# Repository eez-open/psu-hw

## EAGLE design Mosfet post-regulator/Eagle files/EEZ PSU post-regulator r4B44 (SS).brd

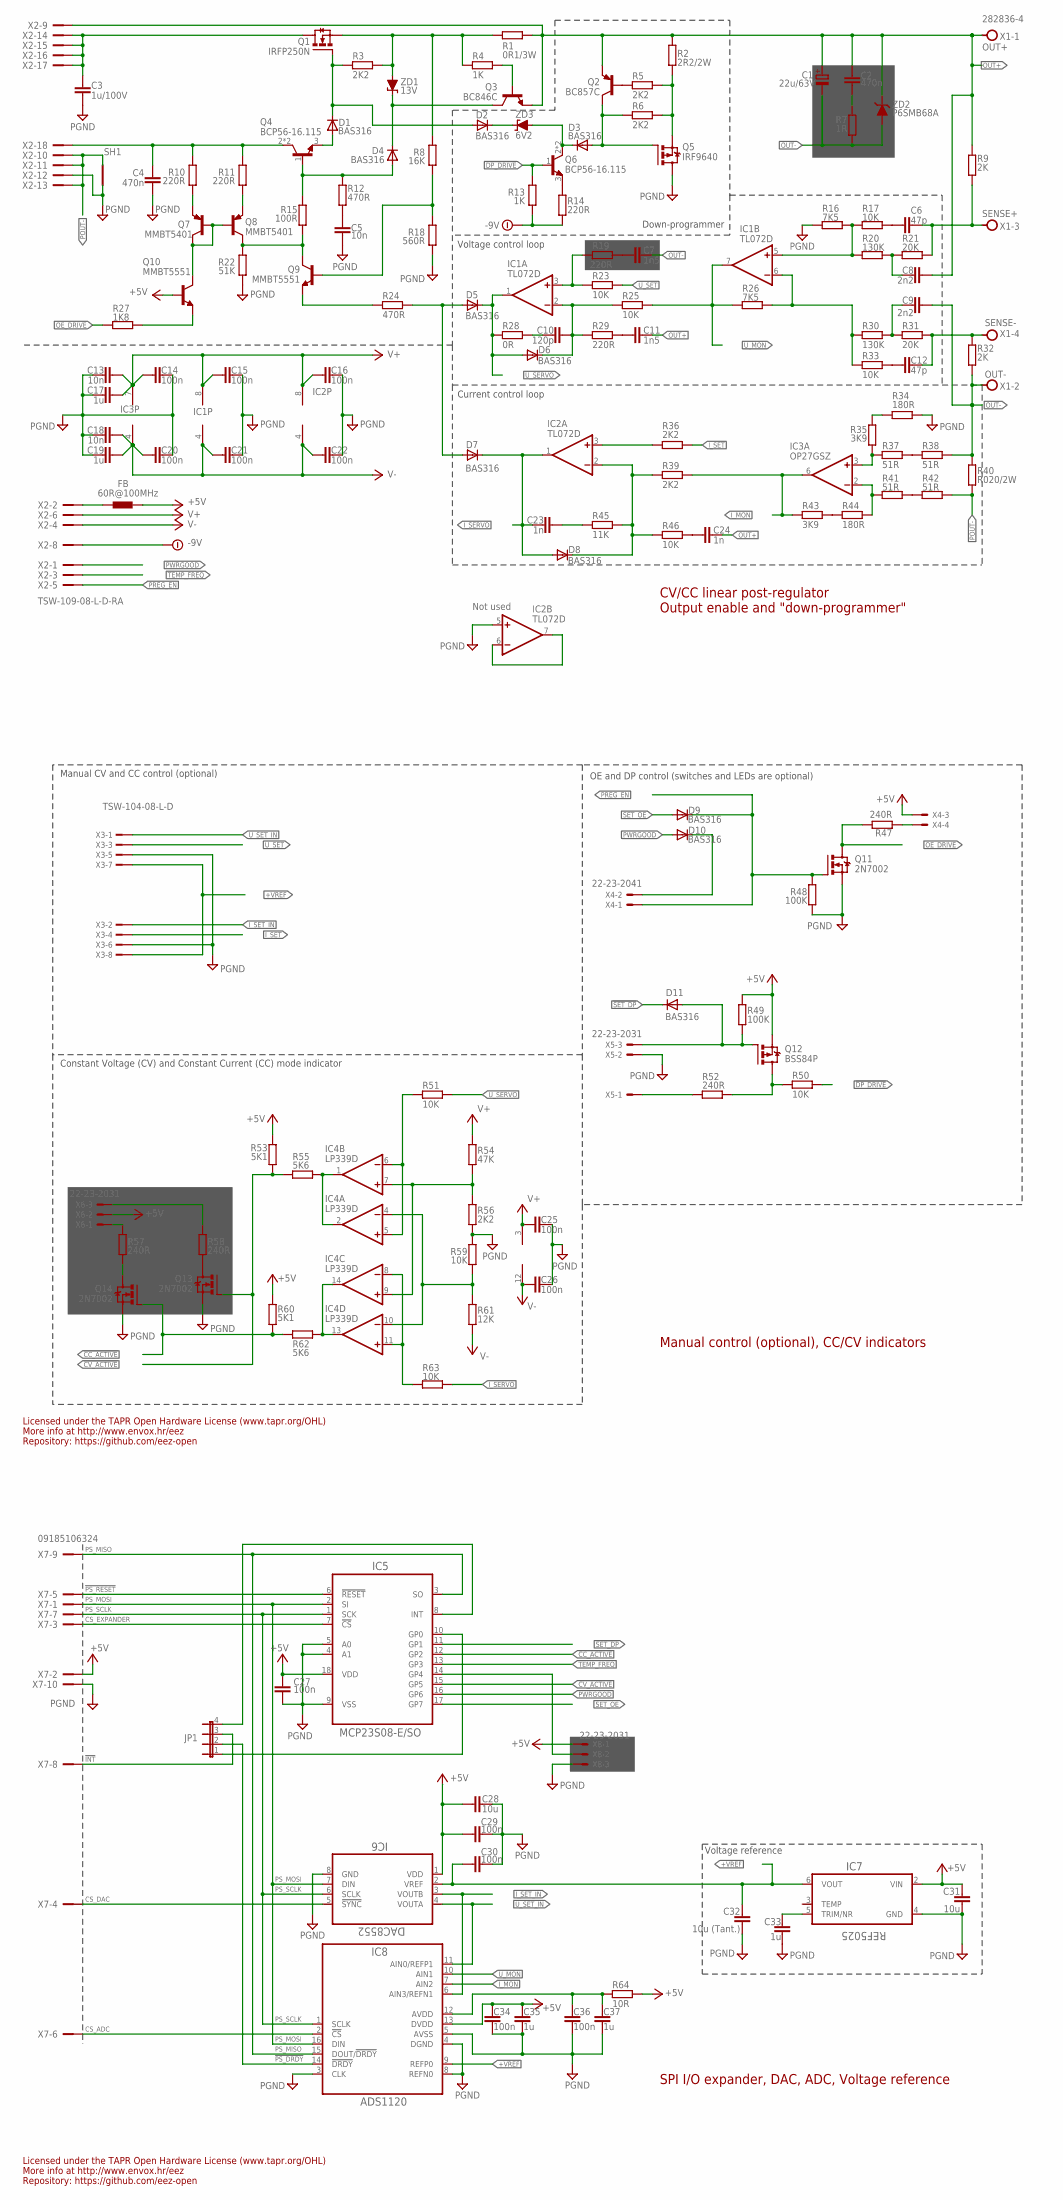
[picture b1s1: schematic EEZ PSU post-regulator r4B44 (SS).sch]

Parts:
C1: 22u/63V; CAPAE660X610N_COMBO2
C2, C4: 470n; C1812
C3: 1u/100V; C1206
C5, C13, C18: 10n; C0805
C6, C12: 47p; C0805
C7, C11: 1n5; C0805
C8, C9: 2n2; C0805
C10: 120p; C0805
C14, C15, C16, C20, C21, C22, C25, C26, C27, C29, C30, C34, C36: 100n; C0603
C17, C19, C33, C35, C37: 1u; C0805
C23, C24: 1n; C0805
C28, C31: 10u; C1206
C32: 10u (Tant.); C1206
D1, D2, D3, D4, D5, D6, D7, D8, D9, D10, D11: BAS316; SOD323-W
FB: 60R@100MHz; BEAD0603
IC1, IC2: TL072D; SOIC127P600X173-8N
IC3: OP27GSZ; SOIC127P600X173-8N
IC4: LP339D; SO14
IC5: MCP23S08-E/SO; SOIC127P1030X265-18N
IC6: DAC8552; DGK8-M
IC7: REF5025; SOIC127P600X175-8N
IC8: ADS1120; PW(R-PDSO-G16)
JP1: JP4E; JP4
Q1: IRFP250N; TO247BV
Q2: BC857C; SOT23-BEC
Q3: BC846C; SOT23-BEC
Q4, Q6: BCP56-16.115; SOT230P700X180-4N
Q5: IRF9640; TO220B-VMOS
Q7, Q8: MMBT5401; SOT23-BEC
Q9, Q10: MMBT5551; SOT23-BEC
Q11: 2N7002; SOT103P240X110-3N; MPN 2N7002-7-F
Q12: BSS84P; SOT95P237X112-3N
Q13, Q14: 2N7002; SOT103P240X110-3N
R1: 0R1/3W; 0411V
R2: 2R2/2W; 0411V
R3, R5, R6, R36, R39, R56: 2K2; R0805
R4, R13: 1K; R0805
R7: 1R; R0805
R8: 16K; R0805
R9, R32: 2K; R0805
R10, R11, R14, R19, R29: 220R; R0805
R12, R24: 470R; R0805
R15: 100R; R0805
R16, R26: 7K5; R0805
R17, R23, R25, R33, R46, R50, R51, R59, R63: 10K; R0805
R18: 560R; R0805
R20, R30: 130K; R0805
R21, R31: 20K; R0805
R22: 51K; R0805
R27: 1K8; R0805
R28: 0R; R0805
R34, R44: 180R; R0805
R35, R43: 3K9; R0805
R37, R38, R41, R42: 51R; R0805
R40: R020/2W; R2512
R45: 11K; R0805
R47, R52, R57, R58: 240R; R0805
R48, R49: 100K; R0805
R53, R60: 5K1; R0805
R54: 47K; R0805
R55, R62: 5K6; R0805
R61: 12K; R0805
R64: 10R; R0805
SH1: GND; SHORT
X1: 282836-4; TBLOCK5.0_4
X2: TSW-109-08-L-D-RA; FARNELL 2032801
X3: TSW-104-08-L-D; TSW-104-02-S-D
X4: 22-23-2041; MPN 22-23-2041
X5, X6, X8: 22-23-2031; MPN 22-23-2031
X7: 09185106324; PAK100/2500-10
ZD1: 13V; MINIMELF
ZD2: P6SMB68A; DO214AA
ZD3: 6V2; MINIMELF

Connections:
!CC_ACTIVE: IC5.12 (GP2), Q14.1 (G), R60.1, R62.2
!CV_ACTIVE: IC5.15 (GP5), Q13.1 (G), R53.1, R55.2
!DP_DRIVE: Q6.1 (B), R13.1, R50.1
!INT: JP1.3, X7.8
!PS_DRDY: IC8.14 (!DRDY), JP1.2
!PS_RESET: IC5.6 (!RESET), X7.5
!SET_DP: D11.C, IC5.11 (GP1)
+5V: C27.1, C28.1, C29.2, C31.1, C34.2, C35.2, FB.P$2 (2), IC5.18 (VDD), IC6.1 (VDD), IC7.2 (VIN), IC8.13 (DVDD), Q10.B, Q12.2 (S), R49.1, R53.2, R60.2, R64.1, X4.3, X6.2, X7.2, X8.1
+VREF: C30.2, C32.1, IC6.2 (VREF), IC7.6 (VOUT), IC8.9 (REFP0), X3.7, X3.8
-9V: R13.2, R14.2, X2.8
BATT_NTC: IC5.14 (GP4), X8.2
CC_LED: R57.2, X6.1
CS_ADC: IC8.2 (!CS), X7.6
CS_DAC: IC6.5 (!SYNC), X7.4
CS_EXPANDER: IC5.7 (!CS), X7.3
CV_LED: R58.1, X6.3
DC_IN: C3.1, Q1.D, X2.14, X2.15, X2.16, X2.17
DP_LED: Q12.3 (D), R50.2, R52.2
GND: C3.2, C4.2, C5.2, C13.1, C14.2, C15.1, C16.1, C17.1, C18.1, C19.1, C20.2, C21.1, C22.1, C25.1, C26.1, C27.2, C28.2, C29.1, C30.1, C31.2, C32.2, C33.2, C34.1, C35.1, C36.1, C37.1, IC2.5 (+IN), IC5.4 (A1), IC5.5 (A0), IC5.9 (VSS), IC6.8 (GND), IC7.4 (GND), IC8.3 (CLK), IC8.4 (DGND), IC8.5 (AVSS), IC8.8 (REFN0), Q5.D, Q11.2 (S), Q13.2 (S), Q14.2 (S), R16.1, R18.1, R22.1, R34.1, R48.1, R56.1, R59.2, SH1.1 (GND_A), X2.12, X3.5, X3.6, X5.2, X7.10, X8.3
INT_EXP: IC5.8 (INT), JP1.4
ISENSE+: IC3.3 (+IN), R35.2, R37.2
ISENSE-: IC3.2 (-IN), R41.2, R44.1
I_MON: IC3.6 (OUT), IC8.7 (AIN2), R39.1, R43.2
I_SERVO: C23.2, D7.C, D8.A, IC2.1 (OUT), R63.1
I_SET: R36.1, X3.4
I_SET_IN: IC6.3 (VOUTB), IC8.6 (AIN3/REFN1), X3.2
unnamed: Q6.3 (E), R14.1
unnamed: Q2.B, R5.2
unnamed: C6.2, R17.1
unnamed: D10.C, X4.2
unnamed: R52.1, X5.1
unnamed: D11.A, Q12.1 (G), R49.2, X5.3
unnamed: Q13.3 (D), R58.2
unnamed: R37.1, R38.2
unnamed: R47.1, X4.4
unnamed: C12.2, R33.1
unnamed: C33.1, IC7.5 (TRIM/NR)
unnamed: FB.P$1 (1), X2.2
unnamed: R41.1, R42.2
unnamed: R43.1, R44.2
unnamed: R34.2, R35.1
unnamed: IC2.6 (-IN), IC2.7 (OUT)
unnamed: C9.1, R30.2, R31.1
unnamed: C10.2, R28.1
unnamed: C24.2, R46.1
unnamed: C7.2, R19.1
unnamed: C11.2, R29.1
unnamed: Q14.3 (D), R57.1
unnamed: IC1.3 (+IN), R19.2, R23.2
unnamed: C10.1, D6.C, IC1.2 (-IN), R25.2, R29.2
unnamed: D8.C, IC2.2 (-IN), R39.2, R45.2, R46.2
unnamed: C36.2, C37.2, IC8.12 (AVDD), R64.2
unnamed: Q9.B, R8.1, R18.2
unnamed: IC4.1 (OUT), IC4.2 (OUT), R55.1
unnamed: IC4.13 (OUT), IC4.14 (OUT), R62.1
unnamed: IC2.3 (+IN), R36.2
unnamed: D5.A, D7.A, R24.1
unnamed: D1.C, D2.A, Q1.G, R3.1
unnamed: D1.A, Q4.3 (E)
unnamed: IC5.10 (GP0), JP1.1
unnamed: D4.A, Q4.1 (B), R12.2, R15.1
unnamed: C5.1, R12.1
unnamed: C8.1, R20.2, R21.1
unnamed: D4.C, Q3.C, ZD1.C
unnamed: D2.C, ZD3.C
unnamed: Q9.E, R24.2
unnamed: Q5.S, R2.1, R5.1, R6.1
unnamed: D3.A, Q2.C, Q5.G, R6.2
unnamed: C2.2, R7.2
unnamed: IC1.5 (+IN), R16.2, R17.2, R20.1
unnamed: IC4.5 (+IN), IC4.6 (-IN), R51.2
unnamed: IC1.6 (-IN), R26.2, R30.1, R33.2
unnamed: IC4.8 (-IN), IC4.11 (+IN), R63.2
unnamed: IC4.7 (+IN), IC4.9 (+IN), R54.1, R56.2
unnamed: C23.1, R45.1
unnamed: IC4.4 (-IN), IC4.10 (-IN), R59.1, R61.2
unnamed: Q8.E, R11.1
unnamed: Q7.E, R10.1
unnamed: Q10.E, R27.2
unnamed: Q3.B, R4.1
OE_DRIVE: Q11.3 (D), R27.1, R47.2
OUT+: C1.1 (+), C1.1.1 (+), C2.1, C8.2, C11.1, C24.1, Q2.E, Q3.E, R1.1, R2.2, R9.1, X1.P$1, X2.9, ZD2.C (1)
OUT-: C1.2 (-), C1.2.1 (-), C7.1, C9.2, R7.1, R32.2, R38.1, R40.1, X1.P$2, ZD2.A (2)
POUT-: R40.2, R42.1, SH1.2 (GND_B), X2.10, X2.11, X2.13
PREG_EN: D9.C, Q11.1 (G), R48.2, X2.5, X4.1
PS_MISO: IC5.3 (SO), IC8.15 (DOUT/!DRDY), X7.9
PS_MOSI: IC5.2 (SI), IC6.7 (DIN), IC8.16 (DIN), X7.1
PS_SCLK: IC5.1 (SCK), IC6.6 (SCLK), IC8.1 (SCLK), X7.7
PWRGOOD: D10.A, IC5.16 (GP6), X2.1
Q4_OUT: Q1.S, R1.2, R3.2, R4.2, R8.2, ZD1.A
Q6C: D3.C, Q6.2 (C), Q6.4 (C), ZD3.A
Q7C: Q7.B, Q7.C, Q8.B, Q10.C
Q8C: Q8.C, Q9.C, R15.2, R22.2
SENSE+: C6.1, R9.2, R21.2, X1.P$3
SENSE-: C12.1, R31.2, R32.1, X1.P$4
SET_OE: D9.A, IC5.17 (GP7)
TEMP_FREQ: IC5.13 (GP3), X2.3
U_MON: IC1.7 (OUT), IC8.10 (AIN1), R25.1, R26.1
U_SERVO: D5.C, D6.A, IC1.1 (OUT), R28.2, R51.1
U_SET: R23.1, X3.3
U_SET_IN: IC6.4 (VOUTA), IC8.11 (AIN0/REFP1), X3.1
V+: C13.2, C14.1, C15.2, C16.2, C17.2, C25.2, IC1.8 (V+), IC2.8 (V+), IC3.7 (V+), IC4.3 (V+), R54.2, X2.6
V-: C18.2, C19.2, C20.1, C21.2, C22.2, C26.2, IC1.4 (V-), IC2.4 (V-), IC3.4 (V-), IC4.12 (GND), R61.1, X2.4
VBIAS: C4.1, Q4.2 (C), Q4.4 (C), R10.2, R11.2, X2.18

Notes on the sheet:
Current control loop
Voltage control loop
CV/CC linear post-regulator
Output enable and "down-programmer"
Down-programmer
Not used
Constant Voltage (CV) and Constant Current (CC) mode indicator
Manual CV and CC control (optional)
Manual control (optional), CC/CV indicators
OE and DP control (switches and LEDs are optional)
Licensed under the TAPR Open Hardware License (www.tapr.org/OHL)
Repository: https://github.com/eez-open
More info at http://www.envox.hr/eez
SPI I/O expander, DAC, ADC, Voltage reference
Voltage reference

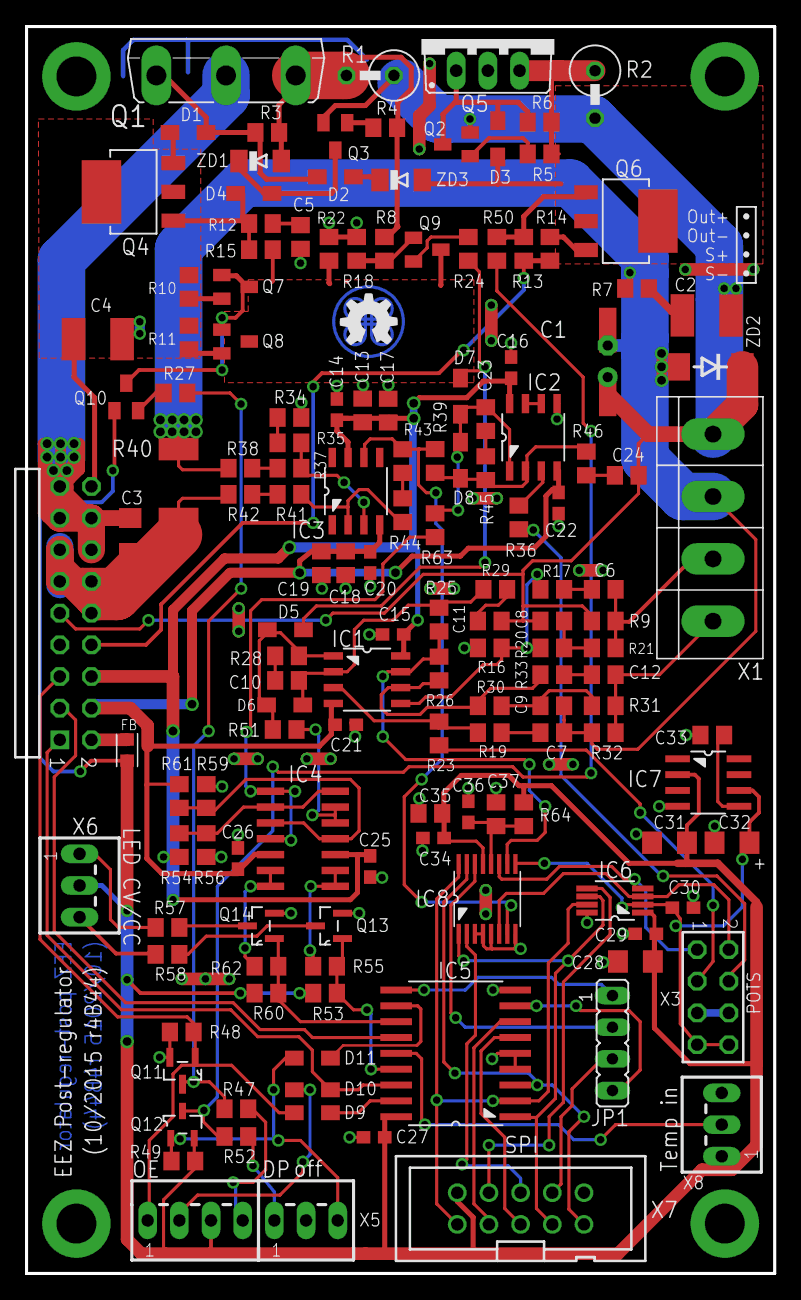
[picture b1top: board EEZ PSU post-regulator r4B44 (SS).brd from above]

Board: 3 copper layers, 60.0 x 100.0 mm, 149 parts (0 on the bottom side), 104 nets.

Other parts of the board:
EEZ_SIGNATURE: SIGNATURESMALL; SIGNATURE_5MM

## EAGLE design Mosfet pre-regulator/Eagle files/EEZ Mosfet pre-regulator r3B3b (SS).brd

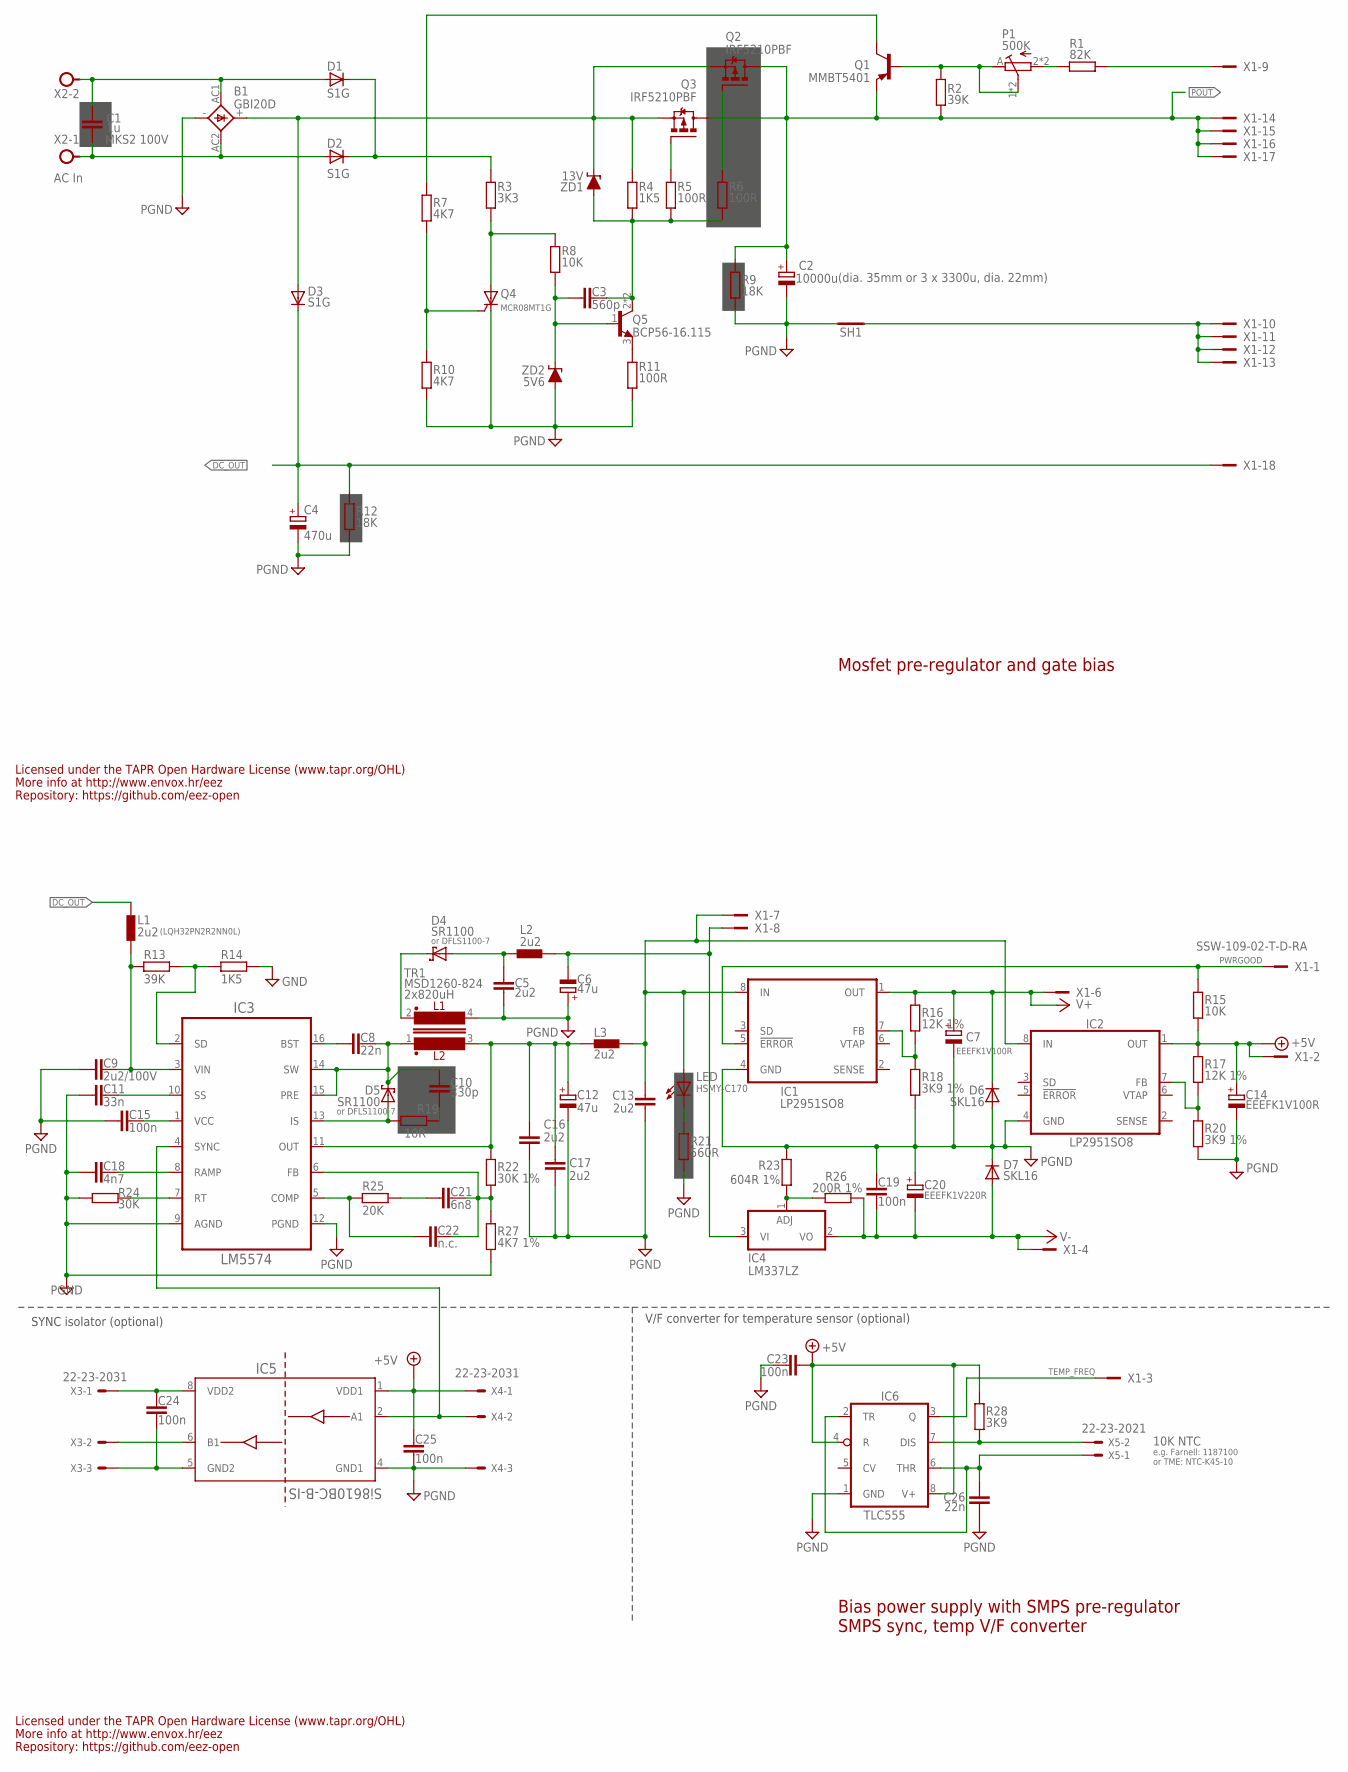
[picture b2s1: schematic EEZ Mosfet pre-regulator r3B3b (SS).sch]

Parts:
B1: GBI20D; GBI20
C1: 1u; C050-075X075
C2: 10000u; ED35D+3XED22.5_COMBO
C3: 560p; C0805
C4: 470u; ECAP5/13
C5, C13, C16, C17: 2u2; C1210
C6, C12: 47u; CAPAE660X610N_COMBO
C7, C14: EEEFK1V100R; CAPAE430X610N_COMBO
C8, C26: 22n; C0805
C9: 2u2/100V; C1210
C10: 330p; C0805
C11: 33n; C0805
C15, C19: 100n; C0805
C18: 4n7; C0805
C20: EEEFK1V220R; CAPAE430X610N_COMBO
C21: 6n8; C0805
C22: n.c.; C0805
C23, C24, C25: 100n; C0603
D1, D2, D3: S1G; DO214AC
D4, D5: SR1100; DO34+SOD123
D6, D7: SKL16; DO214AC
IC1, IC2: LP2951SO8; SOIC127P600X175-8N
IC3: LM5574; SOP65P640X110-16N
IC4: LM337LZ; TO92
IC5: Si8610BC-B-IS; SOIC127P600X173-8N
IC6: TLC555; SOIC127P600X175-8N
L1, L2, L3: 2u2; L1210_COMBO
LED: HSMY-C170; CHIPLED_0805
P1: 500K; R_TRIM+R0805
Q1: MMBT5401; SOT23-BEC
Q2, Q3: IRF5210PBF; TO220B-VMOS
Q4: MCR08MT1G; SOT230P700X180-4N
Q5: BCP56-16.115; SOT230P700X180-4N
R1: 82K; R0805
R2, R13: 39K; R0805
R3: 3K3; R0805
R4, R14: 1K5; R0805
R5, R6, R11: 100R; R0805
R7, R10: 4K7; R0805
R8, R15: 10K; R0805
R9, R12: 18K; R0805
R16, R17: 12K 1%; R0805
R18, R20: 3K9 1%; R0805
R19: 10R; R1210
R21: 560R; R0805
R22: 30K 1%; R0805
R23: 604R 1%; R0805
R24: 30K; R0805
R25: 20K; R0805
R26: 200R 1%; R0805
R27: 4K7 1%; R0805
R28: 3K9; R0805
SH1: SHORTH; SHORT_2
TR1: MSD1260-824; MSD1260
X1: SSW-109-02-T-D-RA; FARNELL 1804359
X2: AC In; TBLOCK5.0_2
X3, X4: 22-23-2031; MPN 22-23-2031
X5: 22-23-2021
ZD1: 13V; MINIMELF
ZD2: 5V6; MINIMELF

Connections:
+5V: C14.1 (+), C14.1.1 (+), C23.1, C25.1, IC2.1 (OUT), IC5.1 (VDD1), IC6.4 (R), IC6.8 (V+), R15.2, R17.1, R28.2, X1.2, X4.1
+VNR: C13.1, IC1.8 (IN), IC2.8 (IN), L3.2, L3.2.1 (2), LED.A, X1.7
-VNR: C6.2 (-), C6.2.1 (-), IC4.3 (VI), L2.2, L2.2.1 (2), X1.8
DC_IN: B1.+, D3.A, Q2.S, Q3.S, R4.1, ZD1.C
DC_OUT: C4.+, D3.C, L1.1, L1.1.1 (1), R12.1, X1.18
DC_PREG1: C9.1, IC3.3 (VIN), L1.2, L1.2.1 (2), R13.2
GND: B1.-, C2.-, C2.-1 (-), C2.-2 (-), C2.-3 (-), C4.-, C5.2, C6.1 (+), C6.1.1 (+), C7.2 (-), C7.2.1 (-), C9.2, C11.2, C12.2 (-), C12.2.1 (-), C13.2, C14.2 (-), C14.2.1 (-), C15.1, C16.2, C17.2, C18.1, C19.1, C20.1 (+), C20.1.1 (+), C23.2, C25.2, C26.1, D6.A, D7.C, IC1.4 (GND), IC2.4 (GND), IC3.9 (AGND), IC3.12 (PGND), IC5.4 (GND1), IC6.1 (GND), Q4.1 (C), R9.2, R10.2, R11.2, R12.2, R14.1, R18.2, R20.2, R21.2, R23.2, R24.2, R27.2, SH1.2 (GND_B), TR1.4, X4.3, ZD2.A
IS: D5.A, D5.A.1 (A), IC3.13 (IS), R19.1
unnamed: Q5.3 (E), R11.1
unnamed: D1.C, D2.C, R3.1
unnamed: Q3.G, R5.1
unnamed: P1.2 (E), P1.E, R1.1
unnamed: Q4.3 (G), R7.2, R10.1
unnamed: C3.2, Q5.1 (B), R8.2, ZD2.C
unnamed: Q2.G, R6.1
unnamed: Q1.C, R7.1
unnamed: LED.C, R21.1
unnamed: SH1.1 (GND_A), X1.10, X1.11, X1.12, X1.13
unnamed: B1.AC1, C1.1, D1.A, X2.2
unnamed: IC1.7 (FB), R16.2, R18.1
unnamed: C10.2, R19.2
unnamed: B1.AC2, C1.2, D2.A, X2.1
unnamed: IC2.7 (FB), R17.2, R20.1
unnamed: C21.2, R25.2
unnamed: P1.1 (S), P1.A, P1.S, Q1.B, R2.1
unnamed: IC5.6 (B1), X3.2
unnamed: C21.1, C22.1, IC3.6 (FB), R22.2, R27.1
unnamed: C8.2, IC3.16 (BST)
unnamed: C22.2, IC3.5 (COMP), R25.1
unnamed: IC3.7 (RT), R24.1
unnamed: C15.2, IC3.1 (VCC)
unnamed: C18.2, IC3.8 (RAMP)
unnamed: C11.1, IC3.10 (SS)
unnamed: C5.1, D4.A, D4.A.1 (A), L2.1, L2.1.1 (1)
unnamed: IC3.2 (SD), R13.1, R14.2
unnamed: R1.2, X1.9
unnamed: IC6.7 (DIS), R28.1, X5.2
unnamed: C26.2, IC6.2 (TR), IC6.6 (THR), X5.1
unnamed: C24.1, IC5.8 (VDD2), X3.1
unnamed: C24.2, IC5.5 (GND2), X3.3
unnamed: IC4.1 (ADJ), R23.1, R26.2
POUT: C2.+, C2.+2 (+), C2.+3 (+), Q1.E, Q2.D, Q3.D, R2.2, R9.1, X1.14, X1.15, X1.16, X1.17
PWRGOOD: IC1.5 (!ERROR), R15.1, X1.1
Q4A: Q4.2 (A), Q4.4 (A), R3.2, R8.1
Q5C: C3.1, Q5.2 (C), Q5.4 (C), R4.2, R5.2, R6.2, ZD1.A
SW: C8.1, C10.1, D5.C, D5.C.1 (C), IC3.14 (SW), IC3.15 (PRE), TR1.1
SYNC: IC3.4 (SYNC), IC5.2 (A1), X4.2
TEMP_FREQ: IC6.3 (Q), X1.3
V+: C7.1 (+), C7.1.1 (+), D6.C, IC1.1 (OUT), R16.1, X1.6
V-: C19.2, C20.2 (-), C20.2.1 (-), D7.A, IC4.2 (VO), R26.1, X1.4
VOUT+: C12.1 (+), C12.1.1 (+), C16.1, C17.1, IC3.11 (OUT), L3.1, L3.1.1 (1), R22.1, TR1.3
VOUT-: D4.C, D4.C.1 (C), TR1.2

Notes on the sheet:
Mosfet pre-regulator and gate bias
(dia. 35mm or 3 x 3300u, dia. 22mm)
MKS2 100V
Licensed under the TAPR Open Hardware License (www.tapr.org/OHL)
Repository: https://github.com/eez-open
More info at http://www.envox.hr/eez
Bias power supply with SMPS pre-regulator
2x820uH
SYNC isolator (optional)
e.g. Farnell: 1187100
10K NTC
or TME: NTC-K45-10
V/F converter for temperature sensor (optional)
or DFLS1100-7
(LQH32PN2R2NN0L)
SMPS sync, temp V/F converter

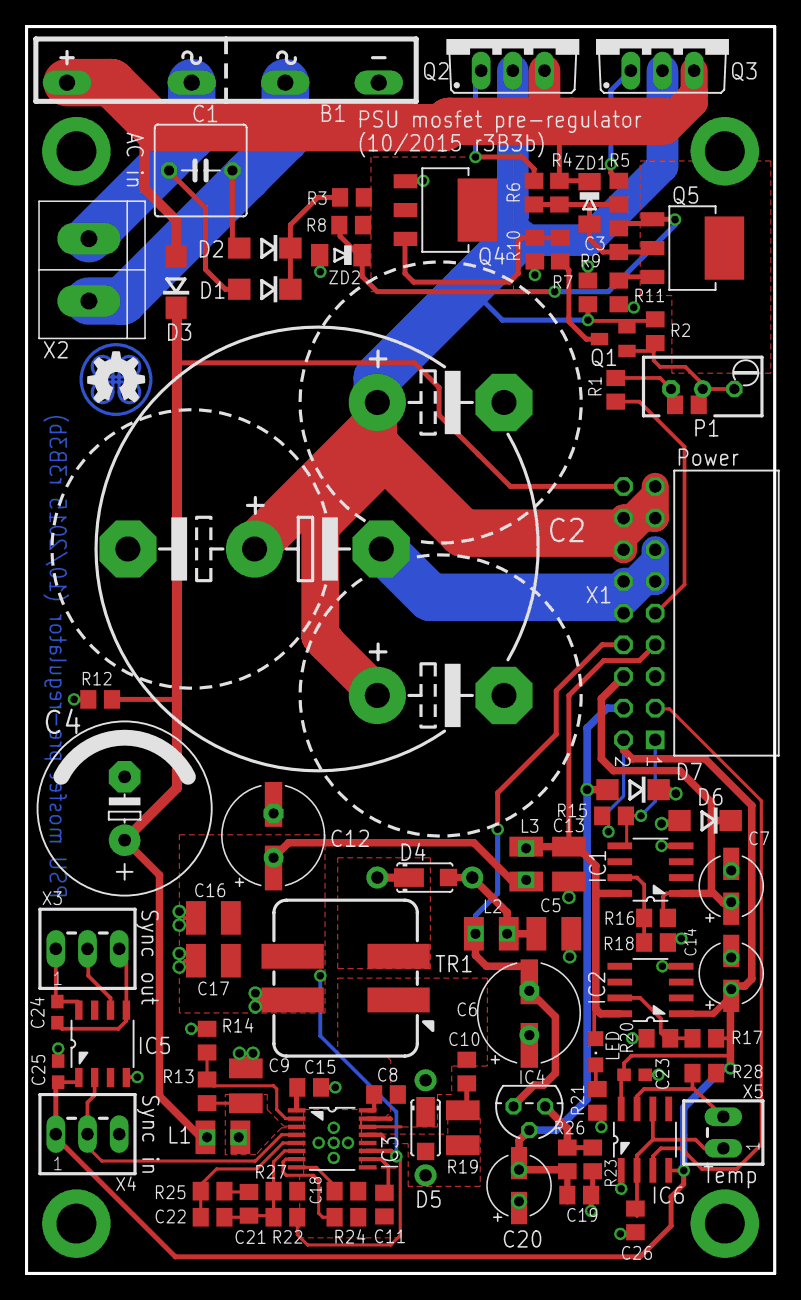
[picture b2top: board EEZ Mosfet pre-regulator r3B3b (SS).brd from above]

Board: 3 copper layers, 60.0 x 100.0 mm, 88 parts (0 on the bottom side), 52 nets.

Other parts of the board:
EEZ_SIGNATURE: SIGNATURESMALL; SIGNATURE_5MM

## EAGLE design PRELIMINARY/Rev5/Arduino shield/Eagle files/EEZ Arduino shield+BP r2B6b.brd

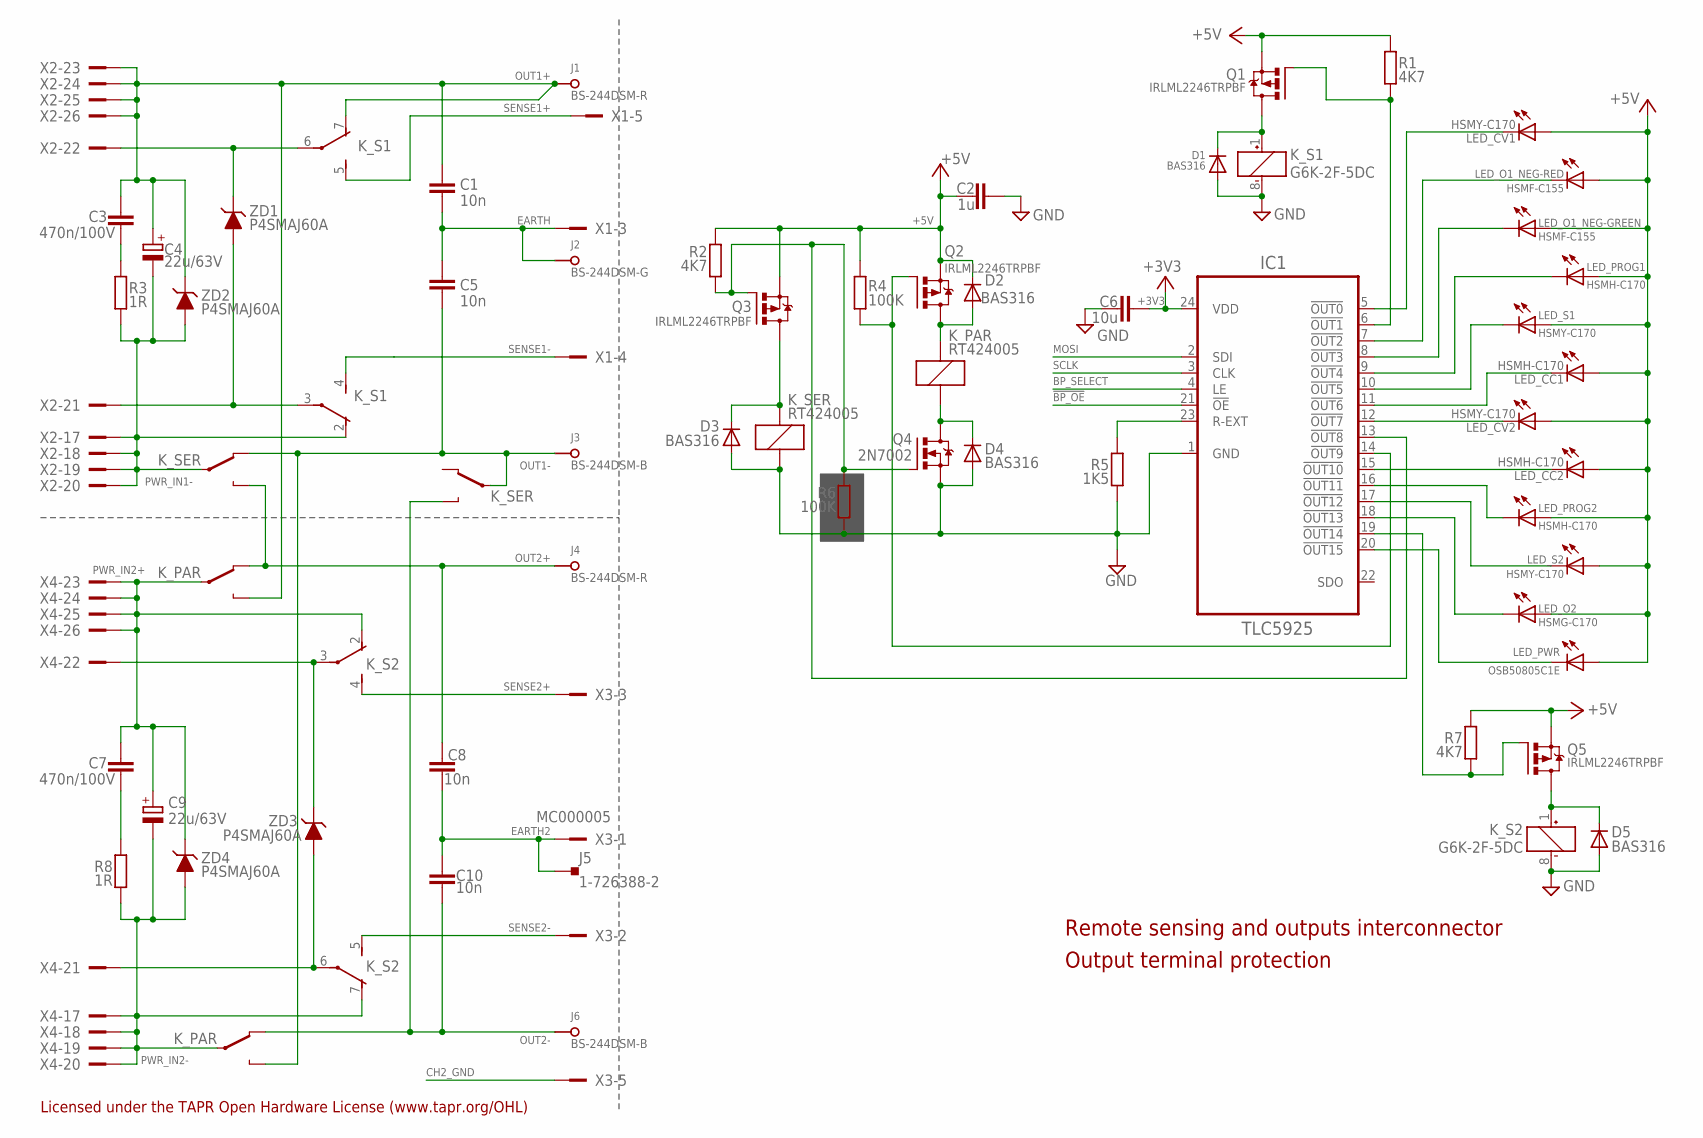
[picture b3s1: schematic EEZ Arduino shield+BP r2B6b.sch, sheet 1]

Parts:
C1, C5, C8, C10: 10n; C1206
C2: 1u; C0805
C3, C7: 470n/100V; C1812
C4, C9: 22u/63V; CAPAE660X610N_COMBO2
C6: 10u; C1206
D1, D2, D3, D4, D5: BAS316; SOD323-W
IC1: TLC5925; SOP63P600X175-24N
J1, J4: BS-244DSM-R; BP_5_12
J2: BS-244DSM-G; BP_5_12
J3, J6: BS-244DSM-B; BP_5_12
J5: 1-726388-2; PCB_TAB-4.8MM
K_PAR: RT424005; RT-C/016A5_ROUND
K_S1, K_S2: G6K-2F-5DC; G6K-2F; MPN G6K-2F DC24
K_SER: RT424005; RT-C/016A5_ROUND
LED_CC1, LED_CC2: HSMH-C170; CHIPLED_0805
LED_CV1, LED_CV2: HSMY-C170; CHIPLED_0805
LED_O1_NEG: HSMF-C155; LED_KPB-3025
LED_O2: HSMG-C170; CHIPLED_0805
LED_PROG1, LED_PROG2: HSMH-C170; CHIPLED_0805
LED_PWR: OSB50805C1E; CHIPLED_0805
LED_S1, LED_S2: HSMY-C170; CHIPLED_0805
Q1, Q2, Q3, Q5: IRLML2246TRPBF; SOT95P237X112-3N
Q4: 2N7002; SOT103P240X110-3N
R1, R2, R7: 4K7; R0805
R3, R8: 1R; R0805
R4, R6: 100K; R0805
R5: 1K5; R0805
X1: MC000006; MC000006_MIRROR; FARNELL 2007972
X2, X4: TSW-113-07-F-D; FARNELL 2025182
X3: MC000005; MC000005_MIRROR
ZD1, ZD2, ZD3, ZD4: P4SMAJ60A; DO214AC

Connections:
!BP_OE: IC1.21 (!OE); also elsewhere on the board
!BP_OUT0: IC1.5 (!OUT0), LED_CV1.C
!BP_OUT1: IC1.6 (!OUT1), Q1.1 (G), R1.1
!BP_OUT2: IC1.7 (!OUT2), LED_O1_NEG.4 (C)
!BP_OUT3: IC1.8 (!OUT3), LED_O1_NEG.2 (C)
!BP_OUT4: IC1.9 (!OUT4), LED_PROG1.C
!BP_OUT5: IC1.10 (!OUT5), LED_S1.C
!BP_OUT6: IC1.11 (!OUT6), LED_CC1.C
!BP_OUT7: IC1.12 (!OUT7), LED_CV2.C
!BP_OUT8: IC1.13 (!OUT8), Q3.1 (G), Q4.1 (G), R2.1, R6.2
!BP_OUT9: IC1.14 (!OUT9), Q2.1 (G), R4.1
!BP_OUT10: IC1.15 (!OUT10), LED_CC2.C
!BP_OUT12: IC1.17 (!OUT12), LED_S2.C
!BP_OUT13: IC1.18 (!OUT13), LED_O2.C
!BP_OUT14: IC1.19 (!OUT14), Q5.1 (G), R7.1
!BP_OUT15: IC1.20 (!OUT15), LED_PWR.C
+3V3: C6.1, IC1.24 (VDD); also elsewhere on the board
+5V: C2.1, D2.C, LED_CC1.A, LED_CC2.A, LED_CV1.A, LED_CV2.A, LED_O1_NEG.1 (A), LED_O1_NEG.3 (A), LED_O2.A, LED_PROG1.A, LED_PROG2.A, LED_PWR.A, LED_S1.A, LED_S2.A, Q1.2 (S), Q2.2 (S), Q3.2 (S), Q5.2 (S), R1.2, R2.2, R4.2, R7.2; also elsewhere on the board
BP_SELECT: IC1.4 (LE); also elsewhere on the board
CH2_GND: X3.5, X3.5.1; also elsewhere on the board
EARTH: C1.2, C5.1, J2.P$1, X1.3, X1.3.1
EARTH2: C8.2, C10.1, J5.P$1, J5.P$2, X3.1, X3.1.1; also elsewhere on the board
GND: C2.2, C6.2, D1.A, D3.A, D4.A, D5.A, IC1.1 (GND), K_S1.8 (-), K_S2.8 (-), K_SER.A1 (C2), Q4.2 (S), R5.1, R6.1; also elsewhere on the board
MOSI: IC1.2 (SDI); also elsewhere on the board
unnamed: D1.C, K_S1.1 (+), Q1.3 (D)
unnamed: D5.C, K_S2.1 (+), Q5.3 (D)
unnamed: C3.2, R3.2
unnamed: C7.2, R8.2
unnamed: IC1.16 (!OUT11), LED_PROG2.C
unnamed: D3.C, K_SER.A2 (C1), Q3.3 (D)
unnamed: D2.A, K_PAR.A2 (C1), Q2.3 (D)
unnamed: IC1.23 (R-EXT), R5.2
OUT1+: C1.1, C3.1, C4.1 (+), C4.1.1 (+), J1.P$1, K_PAR.14B (O), K_S1.7 (O), X2.23, X2.24, X2.25, X2.26, ZD2.C
OUT1-: C5.2, J3.P$1, K_PAR.14A (O), K_SER.11A, K_SER.12B (S)
OUT2+: C8.1, J4.P$1, K_PAR.12B (S), K_SER.14B (O)
OUT2-: C10.2, J6.P$1, K_PAR.12A (S), K_SER.14A (O)
PWR_IN1-: C4.2 (-), C4.2.1 (-), K_S1.2 (O), K_SER.11B, R3.1, X2.17, X2.18, X2.19, X2.20, ZD2.A
PWR_IN2+: C7.1, C9.1 (+), C9.1.1 (+), K_PAR.11B, K_S2.2 (O), X4.23, X4.24, X4.25, X4.26, ZD4.C
PWR_IN2-: C9.2 (-), C9.2.1 (-), K_PAR.11A, K_S2.7 (O), R8.1, X4.17, X4.18, X4.19, X4.20, ZD4.A
SCLK: IC1.3 (CLK); also elsewhere on the board
SENSE1+: K_S1.5 (S), X1.5, X1.5.1
SENSE1-: K_S1.4 (S), X1.4, X1.4.1
SENSE1_IN+: K_S1.6, X2.22, ZD1.C
SENSE1_IN-: K_S1.3, X2.21, ZD1.A
SENSE2+: K_S2.4 (S), X3.3, X3.3.1
SENSE2-: K_S2.5 (S), X3.2, X3.2.1
SENSE2_IN+: K_S2.3, X4.22, ZD3.C
SENSE2_IN-: K_S2.6, X4.21, ZD3.A
V-2: D4.C, K_PAR.A1 (C2), Q4.3 (D)

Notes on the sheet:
Remote sensing and outputs interconnector
Output terminal protection
Licensed under the TAPR Open Hardware License (www.tapr.org/OHL)

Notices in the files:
parts and their libraries:
EEZ_Lib1: This work is licensed under a Creative Commons Attribution-ShareAlike 4.0 International License.
